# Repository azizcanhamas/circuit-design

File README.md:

# circuit-design

# RS485 TTL Converter PCB Draw

# Two Channel Relay Shield PCB Draw

# USB to TTL Converter PCB Draw

# Analog value to binary conversion in Proteus
https://github.com/azizcanhamas/circuit-design/assets/57099416/6f91fc39-c3c1-4516-a9cc-c1eac88dab20

# Read values from four piece 74HC595 and print Serial monitor in Proteus 
https://github.com/azizcanhamas/circuit-design/assets/57099416/ab2cb45f-58f7-40d6-bc80-6174ce0f179c

# Temperature controlled DC motor.
https://github.com/azizcanhamas/circuit-design/assets/57099416/aa9fe6a6-09c7-4acb-a7ce-687bb324d198

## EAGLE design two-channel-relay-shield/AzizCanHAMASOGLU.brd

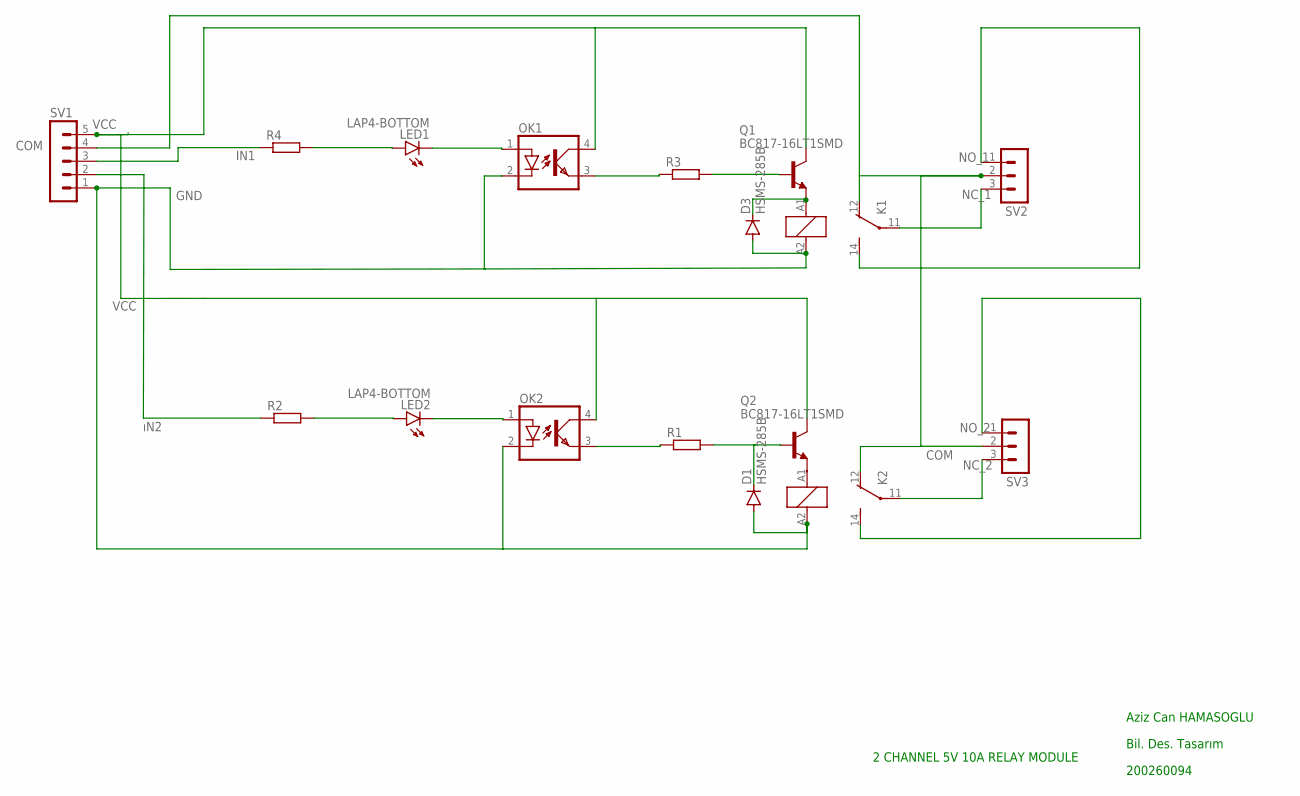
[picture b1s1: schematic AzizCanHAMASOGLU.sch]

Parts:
D1, D3: HSMS-285B; SOT323
K1, K2: RY210005; RY-II
LED1, LED2: LAP4-BOTTOM; P47F-BOTTOM
OK1, OK2: PC817; DIL04
Q1, Q2: BC817-16LT1SMD; SOT23-BEC
R1, R2, R3, R4: R-EU_M1206; M1206
SV1: MA05-1
SV2, SV3: MA03-1

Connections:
COM: K1.12 (O), SV1.4, SV2.2, SV3.2
GND: D1.1 (A), D3.1 (A), K1.A2 (2), K2.A2 (2), OK1.2 (C), OK2.2 (C), SV1.1
IN1: R4.1, SV1.3
unnamed: OK1.3 (EMIT), R3.1
unnamed: LED1.C, OK1.1 (A)
unnamed: Q1.B, R3.2
unnamed: LED1.A, R4.2
unnamed: D3.3 (C), K1.A1 (1), Q1.E
unnamed: OK2.3 (EMIT), R1.1
unnamed: D1.3 (C), Q2.B, R1.2
unnamed: LED2.C, OK2.1 (A)
unnamed: LED2.A, R2.2
NC_1: K1.11, SV2.3
NC_2: K2.11, SV3.3
NO_1: K1.14 (S), SV2.1
NO_2: K2.14 (S), SV3.1
VCC: OK1.4 (COL), OK2.4 (COL), Q1.C, Q2.C, SV1.5
ıN2: R2.1, SV1.2

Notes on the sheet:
Aziz Can HAMASOGLU
Bil. Des. Tasarım
200260094
2 CHANNEL 5V 10A RELAY MODULE

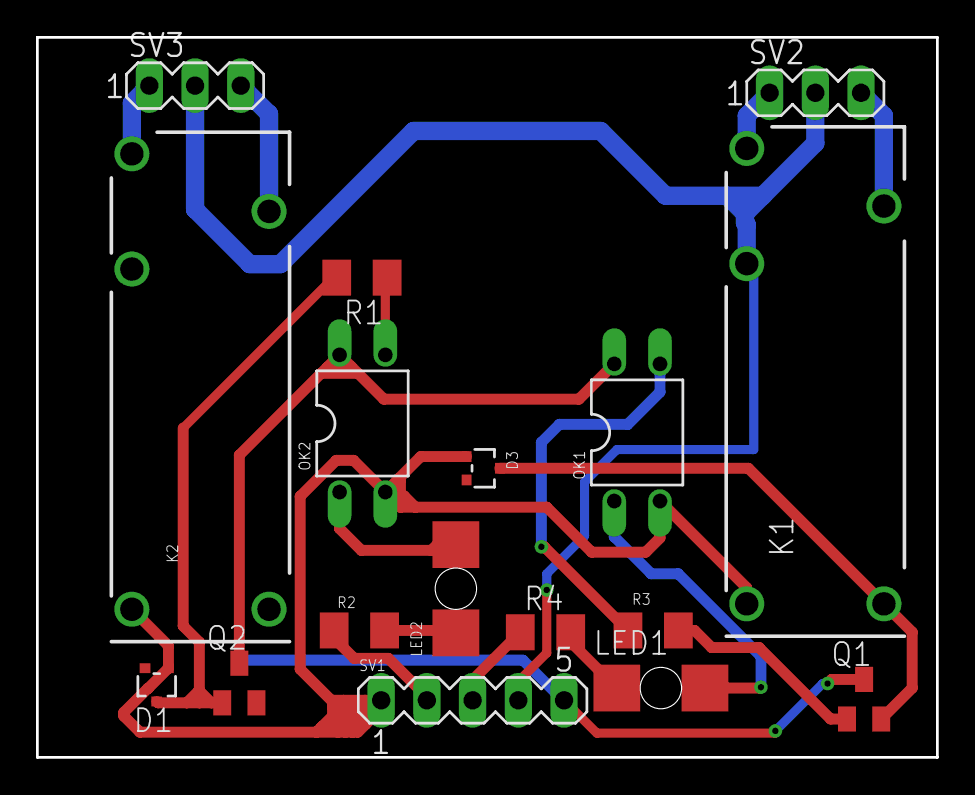
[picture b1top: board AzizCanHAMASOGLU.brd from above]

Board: 2 copper layers, 50.0 x 40.0 mm, 17 parts (0 on the bottom side), 18 nets.

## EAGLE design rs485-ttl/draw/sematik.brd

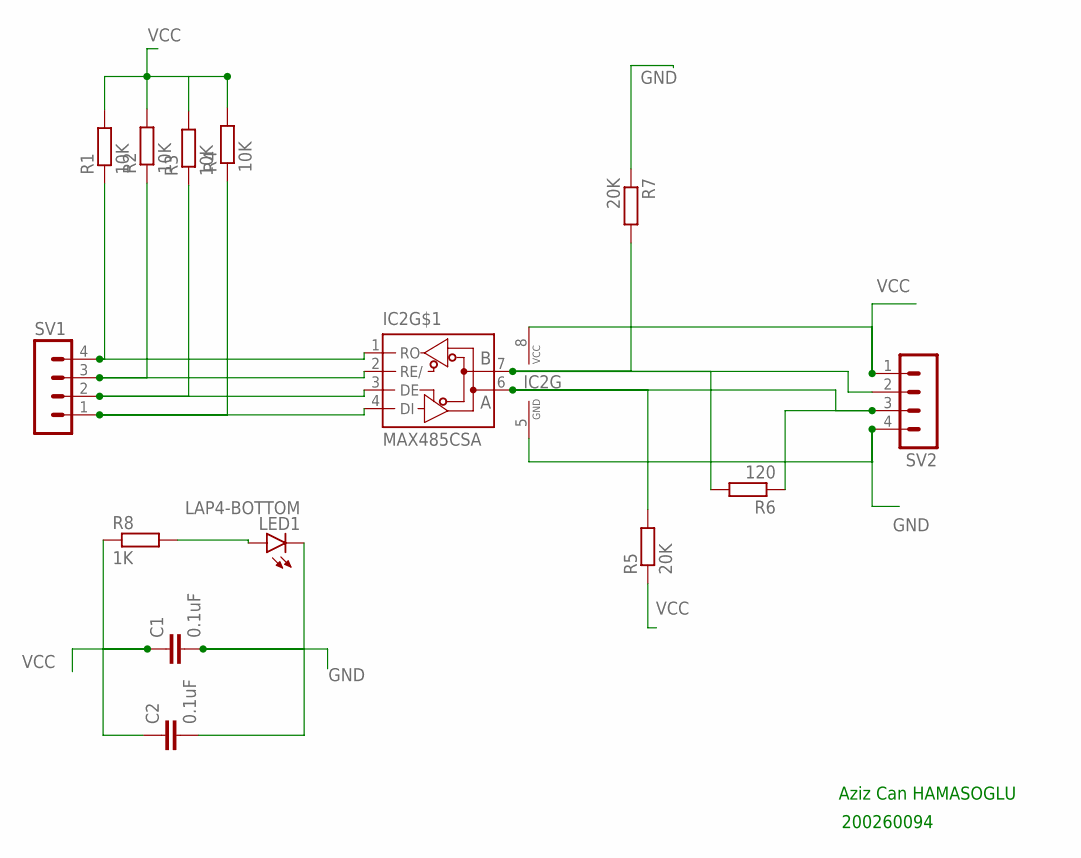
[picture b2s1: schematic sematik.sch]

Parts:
C1, C2: 0.1uF; C0402K
IC2: MAX485CSA; SO08
LED1: LAP4-BOTTOM; P47F-BOTTOM
R1, R2, R3, R4: 10K; M1206
R5, R7: 20K; M1206
R6: 120; M1206
R8: 1K; M1206
SV1, SV2: MA04-1

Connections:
GND: C1.2, C2.2, IC2.5 (GND), LED1.C, R7.1, SV2.4
unnamed: IC2.1 (RO), R1.1, SV1.4
unnamed: IC2.2 (RE/), R2.1, SV1.3
unnamed: IC2.3 (DE), R3.1, SV1.2
unnamed: IC2.4 (DI), R4.1, SV1.1
unnamed: IC2.7 (B), R6.2, R7.2, SV2.2
unnamed: IC2.6 (A), R5.2, R6.1, SV2.3
unnamed: LED1.A, R8.2
VCC: C1.1, C2.1, IC2.8 (VCC), R1.2, R2.2, R3.2, R4.2, R5.1, R8.1, SV2.1

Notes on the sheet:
Aziz Can HAMASOGLU
200260094

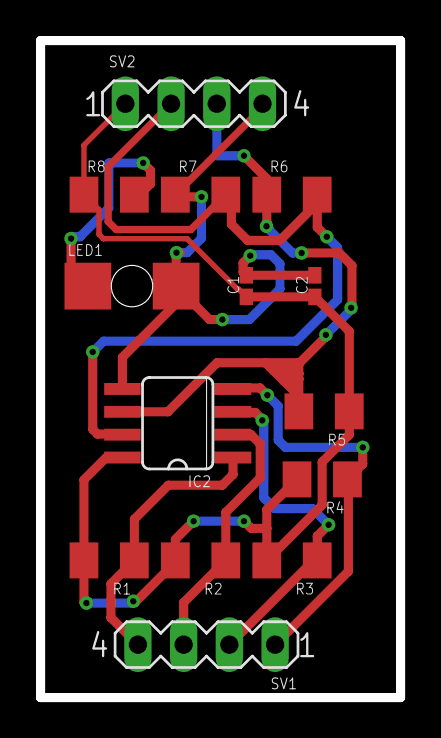
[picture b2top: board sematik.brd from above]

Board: 2 copper layers, 20.0 x 36.5 mm, 14 parts (0 on the bottom side), 9 nets.

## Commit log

2023-07-30 ADD all.
